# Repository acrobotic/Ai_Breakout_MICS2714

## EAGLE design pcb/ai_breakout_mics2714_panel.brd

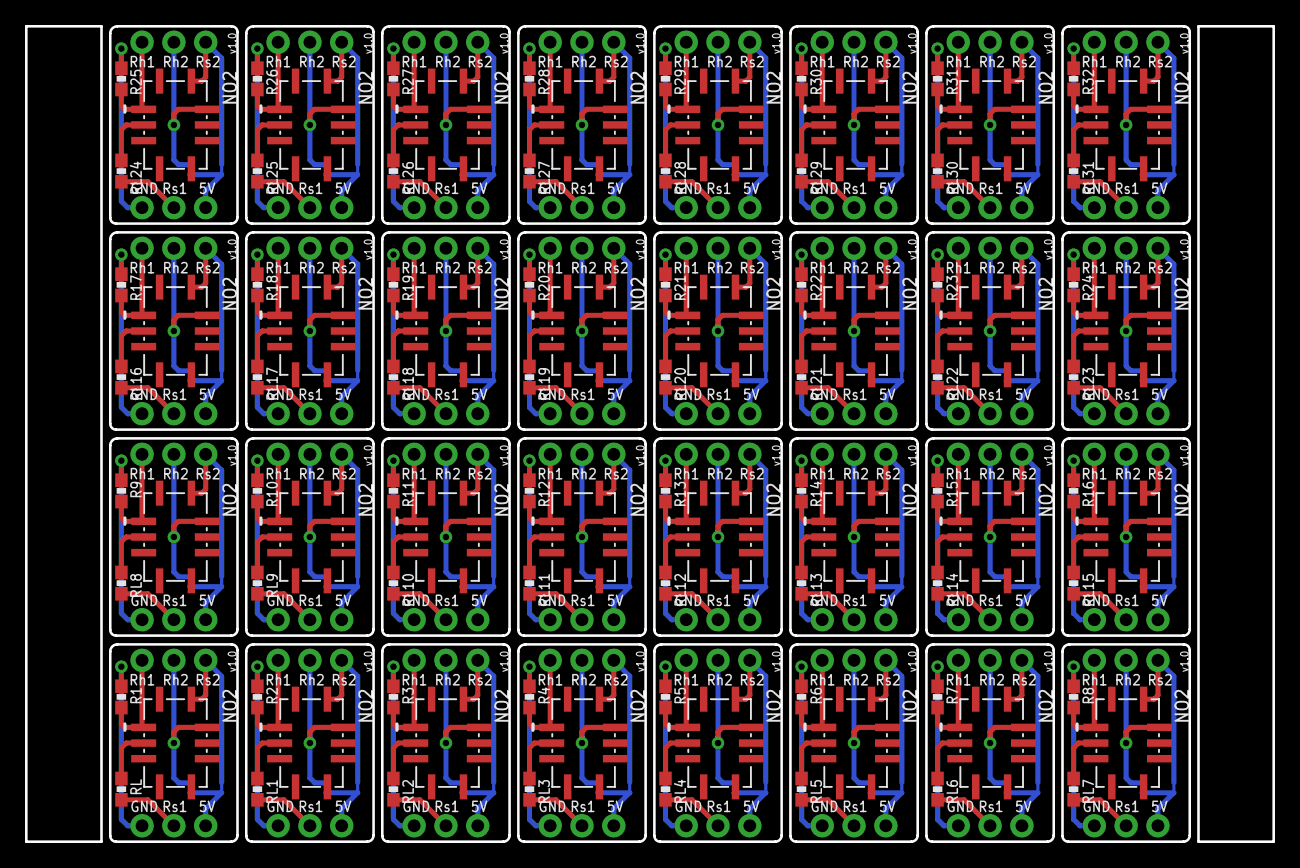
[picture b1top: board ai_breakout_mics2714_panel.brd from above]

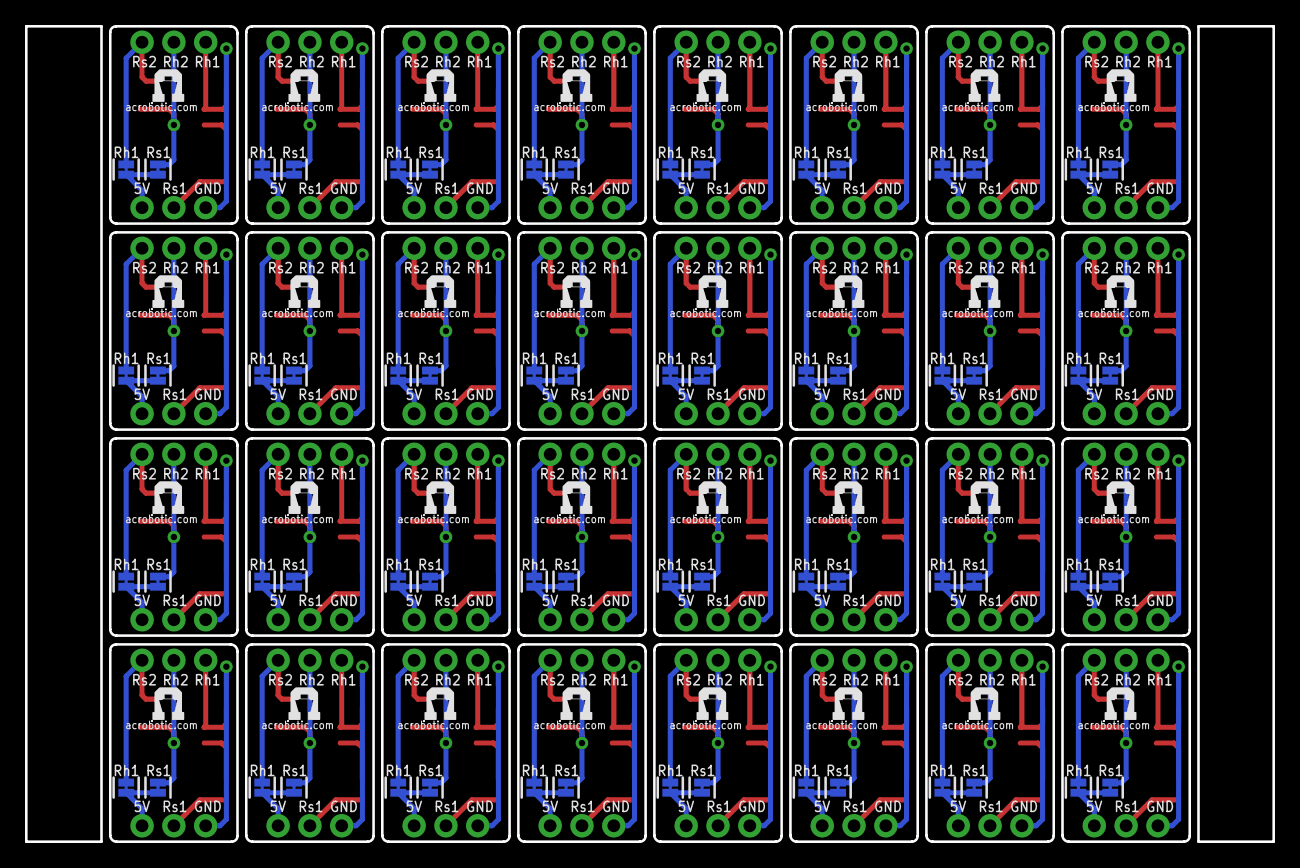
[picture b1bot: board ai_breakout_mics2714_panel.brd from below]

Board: 2 copper layers, 99.6 x 65.1 mm, 256 parts (96 on the bottom side), 224 nets.

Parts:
J1, J2, J3, J4, J5, J6, J7, J8, J9, J10, J11, J12, J13, J14, J15, J16, J17, J18, J19, J20, J21, J22, J23, J24, J25, J26, J27, J28, J29, J30, J31, J32, J33, J34, J35, J36, J37, J38, J39, J40, J41, J42, J43, J44, J45, J46, J47, J48, J49, J50, J51, J52, J53, J54, J55, J56, J57, J58, J59, J60, J61, J62, J63, J64: 1X03NOFIRST; 1X03-NOFIRST
JS1, JS2, JS3, JS4, JS5, JS6, JS7, JS8, JS9, JS10, JS11, JS12, JS13, JS14, JS15, JS16, JS17, JS18, JS19, JS20, JS21, JS22, JS23, JS24, JS25, JS26, JS27, JS28, JS29, JS30, JS31, JS32, JS33, JS34, JS35, JS36, JS37, JS38, JS39, JS40, JS41, JS42, JS43, JS44, JS45, JS46, JS47, JS48, JS49, JS50, JS51, JS52, JS53, JS54, JS55, JS56, JS57, JS58, JS59, JS60, JS61, JS62, JS63, JS64: 1X02-SJ-NCT
R1, R2, R3, R4, R5, R6, R7, R8, R9, R10, R11, R12, R13, R14, R15, R16, R17, R18, R19, R20, R21, R22, R23, R24, R25, R26, R27, R28, R29, R30, R31, R32: 131; RES-0603
RL, RL1, RL2, RL3, RL4, RL5, RL6, RL7, RL8, RL9, RL10, RL11, RL12, RL13, RL14, RL15, RL16, RL17, RL18, RL19, RL20, RL21, RL22, RL23, RL24, RL25, RL26, RL27, RL28, RL29, RL30, RL31: 820; RES-0603
U1, U2, U3, U4, U5, U6, U7, U8, U9, U10, U11, U12, U13, U14, U15, U16, U17, U18, U19, U20, U21, U22, U23, U24, U25, U26, U27, U28, U29, U30, U31, U32: MICS-2714
U$1, U$2, U$3, U$4, U$5, U$6, U$7, U$8, U$9, U$10, U$11, U$12, U$13, U$14, U$15, U$16, U$17, U$18, U$19, U$20, U$21, U$22, U$23, U$24, U$25, U$26, U$27, U$28, U$29, U$30, U$31, U$32: AI-LOGOXS; AI-LOGO-XS

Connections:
5V: J2.1, JS1.2, JS2.2
5V1: J4.1, JS3.2, JS4.2
5V2: J6.1, JS5.2, JS6.2
5V3: J8.1, JS7.2, JS8.2
5V4: J10.1, JS9.2, JS10.2
5V5: J12.1, JS11.2, JS12.2
5V6: J14.1, JS13.2, JS14.2
5V7: J16.1, JS15.2, JS16.2
5V8: J18.1, JS17.2, JS18.2
5V9: J20.1, JS19.2, JS20.2
5V10: J22.1, JS21.2, JS22.2
5V11: J24.1, JS23.2, JS24.2
5V12: J26.1, JS25.2, JS26.2
5V13: J28.1, JS27.2, JS28.2
5V14: J30.1, JS29.2, JS30.2
5V15: J32.1, JS31.2, JS32.2
5V16: J34.1, JS33.2, JS34.2
5V17: J36.1, JS35.2, JS36.2
5V18: J38.1, JS37.2, JS38.2
5V19: J40.1, JS39.2, JS40.2
5V20: J42.1, JS41.2, JS42.2
5V21: J44.1, JS43.2, JS44.2
5V22: J46.1, JS45.2, JS46.2
5V23: J48.1, JS47.2, JS48.2
5V24: J50.1, JS49.2, JS50.2
5V25: J52.1, JS51.2, JS52.2
5V26: J54.1, JS53.2, JS54.2
5V27: J56.1, JS55.2, JS56.2
5V28: J58.1, JS57.2, JS58.2
5V29: J60.1, JS59.2, JS60.2
5V30: J62.1, JS61.2, JS62.2
5V31: J64.1, JS63.2, JS64.2
A/RH1: J1.3, R1.2, U1.A
A/RH2: J3.3, R2.2, U2.A
A/RH3: J5.3, R3.2, U3.A
A/RH4: J7.3, R4.2, U4.A
A/RH5: J9.3, R5.2, U5.A
A/RH6: J11.3, R6.2, U6.A
A/RH7: J13.3, R7.2, U7.A
A/RH8: J15.3, R8.2, U8.A
A/RH9: J17.3, R9.2, U9.A
A/RH10: J19.3, R10.2, U10.A
A/RH11: J21.3, R11.2, U11.A
A/RH12: J23.3, R12.2, U12.A
A/RH13: J25.3, R13.2, U13.A
A/RH14: J27.3, R14.2, U14.A
A/RH15: J29.3, R15.2, U15.A
A/RH16: J31.3, R16.2, U16.A
A/RH17: J33.3, R17.2, U17.A
A/RH18: J35.3, R18.2, U18.A
A/RH19: J37.3, R19.2, U19.A
A/RH20: J39.3, R20.2, U20.A
A/RH21: J41.3, R21.2, U21.A
A/RH22: J43.3, R22.2, U22.A
A/RH23: J45.3, R23.2, U23.A
A/RH24: J47.3, R24.2, U24.A
A/RH25: J49.3, R25.2, U25.A
A/RH26: J51.3, R26.2, U26.A
A/RH27: J53.3, R27.2, U27.A
A/RH28: J55.3, R28.2, U28.A
A/RH29: J57.3, R29.2, U29.A
A/RH30: J59.3, R30.2, U30.A
A/RH31: J61.3, R31.2, U31.A
A/RH32: J63.3, R32.2, U32.A
B/RS1: J2.2, RL.2
B/RS2: J4.2, RL1.2
B/RS3: J6.2, RL2.2
B/RS4: J8.2, RL3.2
B/RS5: J10.2, RL4.2
B/RS6: J12.2, RL5.2
B/RS7: J14.2, RL6.2
B/RS8: J16.2, RL7.2
B/RS9: J18.2, RL8.2
B/RS10: J20.2, RL9.2
B/RS11: J22.2, RL10.2
B/RS12: J24.2, RL11.2
B/RS13: J26.2, RL12.2
B/RS14: J28.2, RL13.2
B/RS15: J30.2, RL14.2
B/RS16: J32.2, RL15.2
B/RS17: J34.2, RL16.2
B/RS18: J36.2, RL17.2
B/RS19: J38.2, RL18.2
B/RS20: J40.2, RL19.2
B/RS21: J42.2, RL20.2
B/RS22: J44.2, RL21.2
B/RS23: J46.2, RL22.2
B/RS24: J48.2, RL23.2
B/RS25: J50.2, RL24.2
B/RS26: J52.2, RL25.2
B/RS27: J54.2, RL26.2
B/RS28: J56.2, RL27.2
B/RS29: J58.2, RL28.2
B/RS30: J60.2, RL29.2
B/RS31: J62.2, RL30.2
B/RS32: J64.2, RL31.2
GND: J2.3, R1.1
GND1: J4.3, R2.1
GND2: J6.3, R3.1
GND3: J8.3, R4.1
GND4: J10.3, R5.1
GND5: J12.3, R6.1
GND6: J14.3, R7.1
GND7: J16.3, R8.1
GND8: J18.3, R9.1
GND9: J20.3, R10.1
GND10: J22.3, R11.1
GND11: J24.3, R12.1
GND12: J26.3, R13.1
GND13: J28.3, R14.1
GND14: J30.3, R15.1
GND15: J32.3, R16.1
GND16: J34.3, R17.1
GND17: J36.3, R18.1
GND18: J38.3, R19.1
GND19: J40.3, R20.1
GND20: J42.3, R21.1
GND21: J44.3, R22.1
GND22: J46.3, R23.1
GND23: J48.3, R24.1
GND24: J50.3, R25.1
GND25: J52.3, R26.1
GND26: J54.3, R27.1
GND27: J56.3, R28.1
GND28: J58.3, R29.1
GND29: J60.3, R30.1
GND30: J62.3, R31.1
GND31: J64.3, R32.1
H/RH1: J3.2, JS4.1, U2.H
H/RH2: J1.2, JS2.1, U1.H
H/RH3: J5.2, JS6.1, U3.H
H/RH4: J7.2, JS8.1, U4.H
H/RH5: J9.2, JS10.1, U5.H
H/RH6: J11.2, JS12.1, U6.H
H/RH7: J13.2, JS14.1, U7.H
H/RH8: J15.2, JS16.1, U8.H
H/RH9: J17.2, JS18.1, U9.H
H/RH10: J19.2, JS20.1, U10.H
H/RH11: J21.2, JS22.1, U11.H
H/RH12: J23.2, JS24.1, U12.H
H/RH13: J25.2, JS26.1, U13.H
H/RH14: J27.2, JS28.1, U14.H
H/RH15: J29.2, JS30.1, U15.H
H/RH16: J31.2, JS32.1, U16.H
H/RH17: J33.2, JS34.1, U17.H
H/RH18: J35.2, JS36.1, U18.H
H/RH19: J37.2, JS38.1, U19.H
H/RH20: J39.2, JS40.1, U20.H
H/RH21: J41.2, JS42.1, U21.H
H/RH22: J43.2, JS44.1, U22.H
H/RH23: J45.2, JS46.1, U23.H
H/RH24: J47.2, JS48.1, U24.H
H/RH25: J49.2, JS50.1, U25.H
H/RH26: J51.2, JS52.1, U26.H
H/RH27: J53.2, JS54.1, U27.H
H/RH28: J55.2, JS56.1, U28.H
H/RH29: J57.2, JS58.1, U29.H
H/RH30: J59.2, JS60.1, U30.H
H/RH31: J61.2, JS62.1, U31.H
H/RH32: J63.2, JS64.1, U32.H
J/RS1: J3.1, JS3.1, U2.J
J/RS2: J1.1, JS1.1, U1.J
J/RS3: J5.1, JS5.1, U3.J
J/RS4: J7.1, JS7.1, U4.J
J/RS5: J9.1, JS9.1, U5.J
J/RS6: J11.1, JS11.1, U6.J
J/RS7: J13.1, JS13.1, U7.J
J/RS8: J15.1, JS15.1, U8.J
J/RS9: J17.1, JS17.1, U9.J
J/RS10: J19.1, JS19.1, U10.J
J/RS11: J21.1, JS21.1, U11.J
J/RS12: J23.1, JS23.1, U12.J
J/RS13: J25.1, JS25.1, U13.J
J/RS14: J27.1, JS27.1, U14.J
J/RS15: J29.1, JS29.1, U15.J
J/RS16: J31.1, JS31.1, U16.J
J/RS17: J33.1, JS33.1, U17.J
J/RS18: J35.1, JS35.1, U18.J
J/RS19: J37.1, JS37.1, U19.J
J/RS20: J39.1, JS39.1, U20.J
J/RS21: J41.1, JS41.1, U21.J
J/RS22: J43.1, JS43.1, U22.J
J/RS23: J45.1, JS45.1, U23.J
J/RS24: J47.1, JS47.1, U24.J
J/RS25: J49.1, JS49.1, U25.J
J/RS26: J51.1, JS51.1, U26.J
J/RS27: J53.1, JS53.1, U27.J
J/RS28: J55.1, JS55.1, U28.J
J/RS29: J57.1, JS57.1, U29.J
J/RS30: J59.1, JS59.1, U30.J
J/RS31: J61.1, JS61.1, U31.J
J/RS32: J63.1, JS63.1, U32.J
unnamed: RL.1, U1.B
unnamed: RL1.1, U2.B
unnamed: RL2.1, U3.B
unnamed: RL3.1, U4.B
unnamed: RL4.1, U5.B
unnamed: RL5.1, U6.B
unnamed: RL6.1, U7.B
unnamed: RL7.1, U8.B
unnamed: RL8.1, U9.B
unnamed: RL9.1, U10.B
unnamed: RL10.1, U11.B
unnamed: RL11.1, U12.B
unnamed: RL12.1, U13.B
unnamed: RL13.1, U14.B
unnamed: RL14.1, U15.B
unnamed: RL15.1, U16.B
unnamed: RL16.1, U17.B
unnamed: RL17.1, U18.B
unnamed: RL18.1, U19.B
unnamed: RL19.1, U20.B
unnamed: RL20.1, U21.B
unnamed: RL21.1, U22.B
unnamed: RL22.1, U23.B
unnamed: RL23.1, U24.B
unnamed: RL24.1, U25.B
unnamed: RL25.1, U26.B
unnamed: RL26.1, U27.B
unnamed: RL27.1, U28.B
unnamed: RL28.1, U29.B
unnamed: RL29.1, U30.B
unnamed: RL30.1, U31.B
unnamed: RL31.1, U32.B
